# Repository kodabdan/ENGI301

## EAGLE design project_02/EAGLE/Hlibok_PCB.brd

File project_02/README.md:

Etch-A-Sketch PCB by Brendan Hlibok, 2023

This project consists of a 4-layer PCB designed by Brendan Hlibok using EAGLE software.
The PCB functions as an etch-a-sketch when manufactured. More specific information on this can be found in the
powerpoint presentation under project_02/docs.

The board is 4" tall and 5" wide. The library, schematic, and board layout files can be found in the "EAGLE" folder, and the gerber files for manufacturing
the PCB. The "docs" folder contains descriptive information such as images of important layers, the schematics,
the board layout, and a bill of materials for the product. The bill of materials is in .txt and .csv format, where the .txt
file came straight from the EAGLE software, and the excel file has more specific info regarding component parts.

The board file can be uploaded to manufacturing sites to check quotes for building the board. The site used for this project was
MacroFab.

This project was completed as a part of the ENGI 301 course at Rice University taught by Erik Welsh, who designed the circuit
for the PCB in this file.

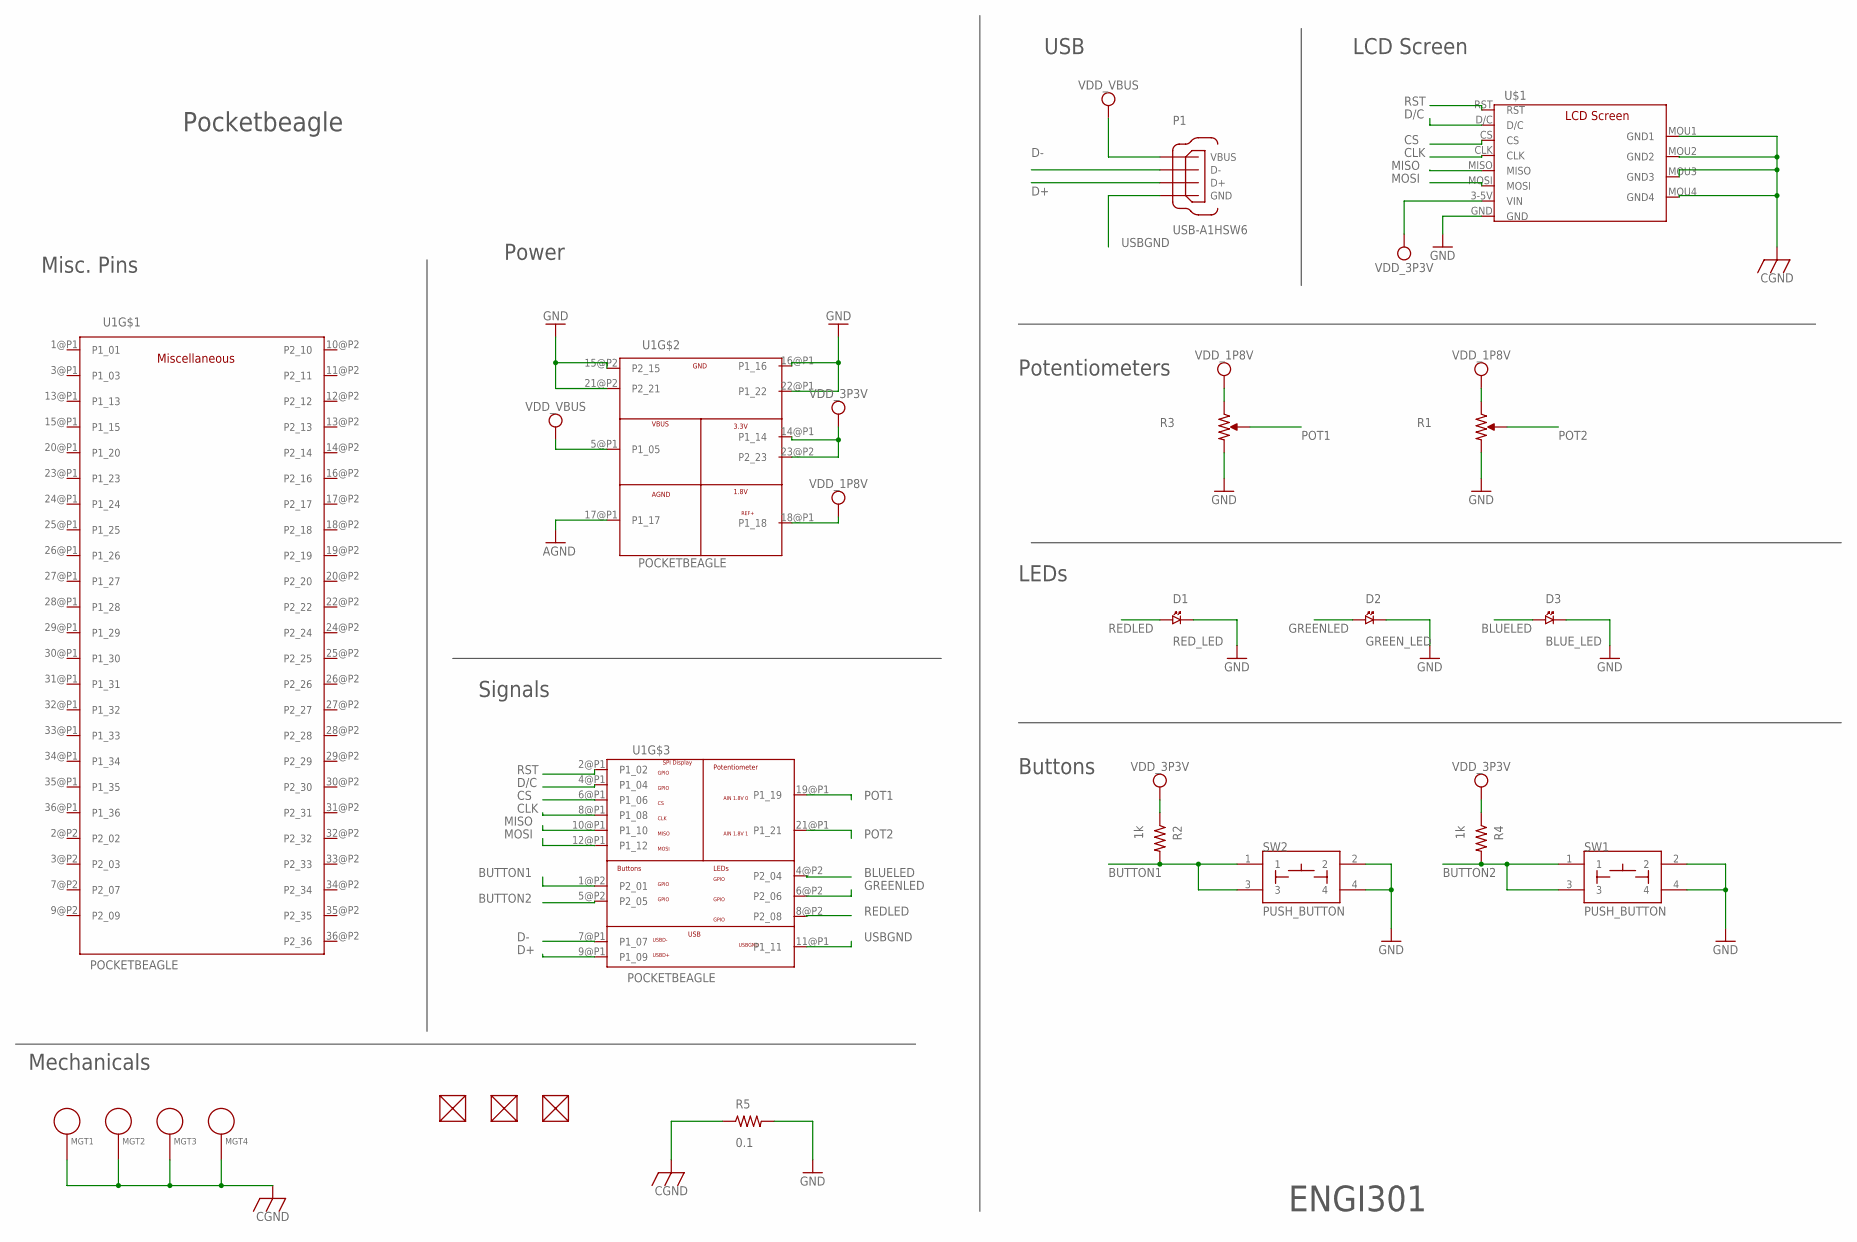
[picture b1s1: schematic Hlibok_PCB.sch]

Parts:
D1: RED_LED; EIA-STD
D2: GREEN_LED; EIA-STD
D3: BLUE_LED; EIA-STD
FUD1, FUD2, FUD3: FIDUCIAL; FIDUCIAL_40MIL
MGT1, MGT2, MGT3, MGT4: MOUNTING_HOLE
P1: USB-A1HSW6; USB
R1, R3: POTENTIOMETER; POT-PO90S
R2, R4: 1k; R0603
R5: 0.1; R0805
SW1, SW2: PUSH_BUTTON; BUTTON_12.5MM
U1: POCKETBEAGLE
U$1: SCREEN

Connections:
BLUELED: D3.ANODE, U1.4@P2 (P2_04)
BUTTON1: R2.2, SW2.1, SW2.3, U1.1@P2 (P2_01)
BUTTON2: R4.2, SW1.1, SW1.3, U1.5@P2 (P2_05)
CGND: MGT1.P$1, MGT2.P$1, MGT3.P$1, MGT4.P$1, R5.1, U$1.MOU1 (GND1), U$1.MOU2 (GND2), U$1.MOU3 (GND3), U$1.MOU4 (GND4)
CLK: U1.8@P1 (P1_08), U$1.CLK
CS: U1.6@P1 (P1_06), U$1.CS
D+: P1.3 (D+), U1.9@P1 (P1_09)
D-: P1.2 (D-), U1.7@P1 (P1_07)
D/C: U1.4@P1 (P1_04), U$1.D/C
GND: D1.CATHODE, D2.CATHODE, D3.CATHODE, R1.CW, R3.CW, R5.2, SW1.2, SW1.4, SW2.2, SW2.4, U1.15@P2 (P2_15), U1.16@P1 (P1_16), U1.17@P1 (P1_17), U1.21@P2 (P2_21), U1.22@P1 (P1_22), U$1.GND
GREENLED: D2.ANODE, U1.6@P2 (P2_06)
MISO: U1.10@P1 (P1_10), U$1.MISO
MOSI: U1.12@P1 (P1_12), U$1.MOSI
POT1: R3.S, U1.19@P1 (P1_19)
POT2: R1.S, U1.21@P1 (P1_21)
REDLED: D1.ANODE, U1.8@P2 (P2_08)
RST: U1.2@P1 (P1_02), U$1.RST
USBGND: P1.4 (GND), U1.11@P1 (P1_11)
VDD_1P8V: R1.CCW, R3.CCW, U1.18@P1 (P1_18)
VDD_3P3V: R2.1, R4.1, U1.14@P1 (P1_14), U1.23@P2 (P2_23), U$1.3-5V (VIN)
VDD_5V: P1.1 (VBUS), U1.5@P1 (P1_05)

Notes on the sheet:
Power
Signals
Misc. Pins
Pocketbeagle
USB
Potentiometers
LEDs
Buttons
LCD Screen
ENGI301
Mechanicals

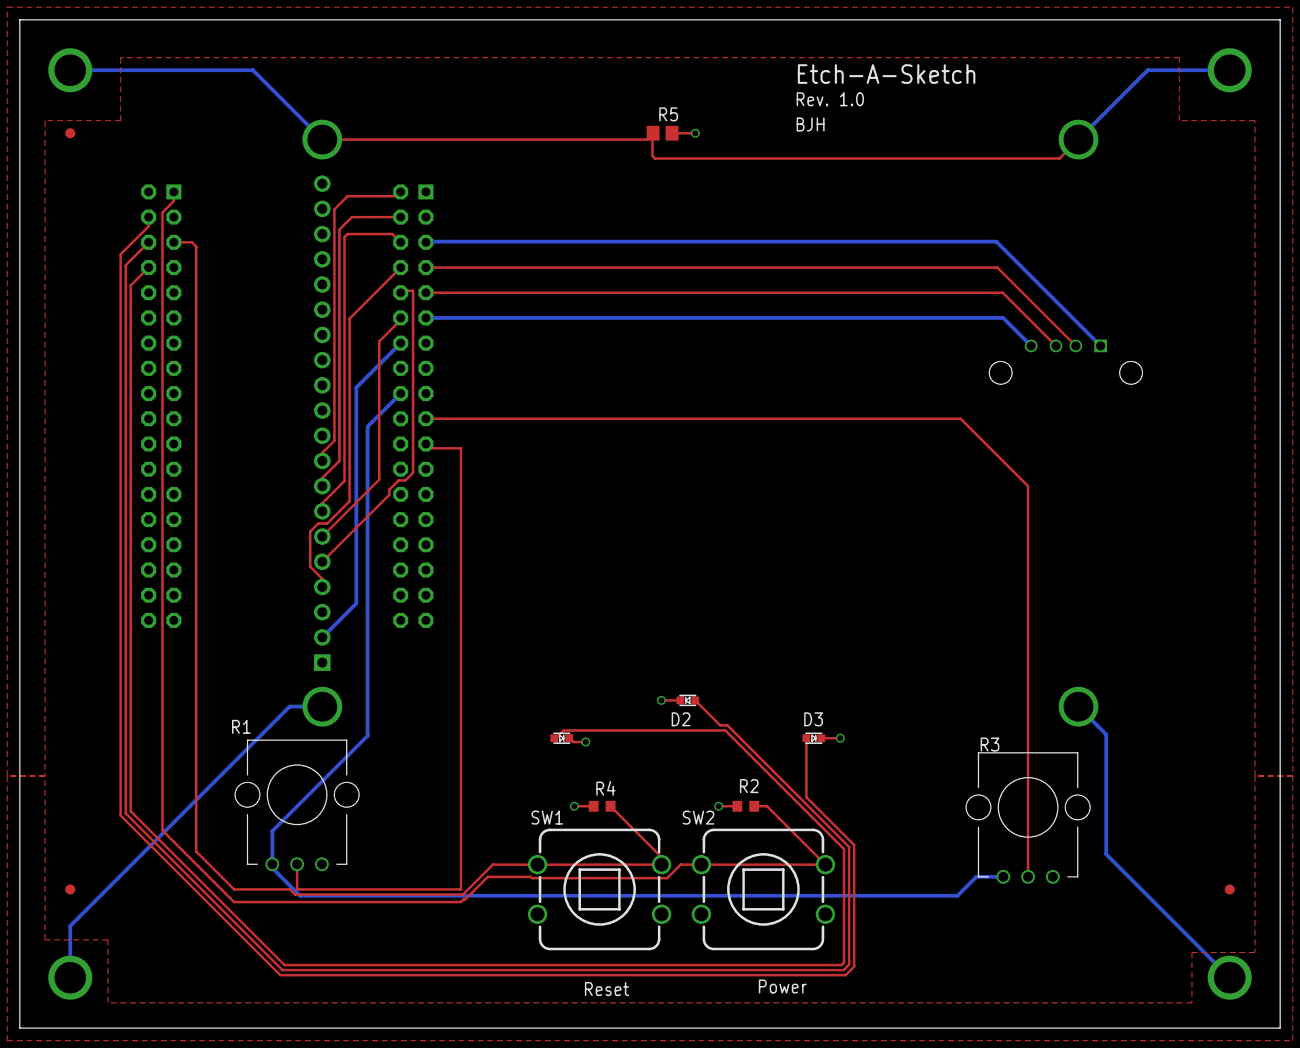
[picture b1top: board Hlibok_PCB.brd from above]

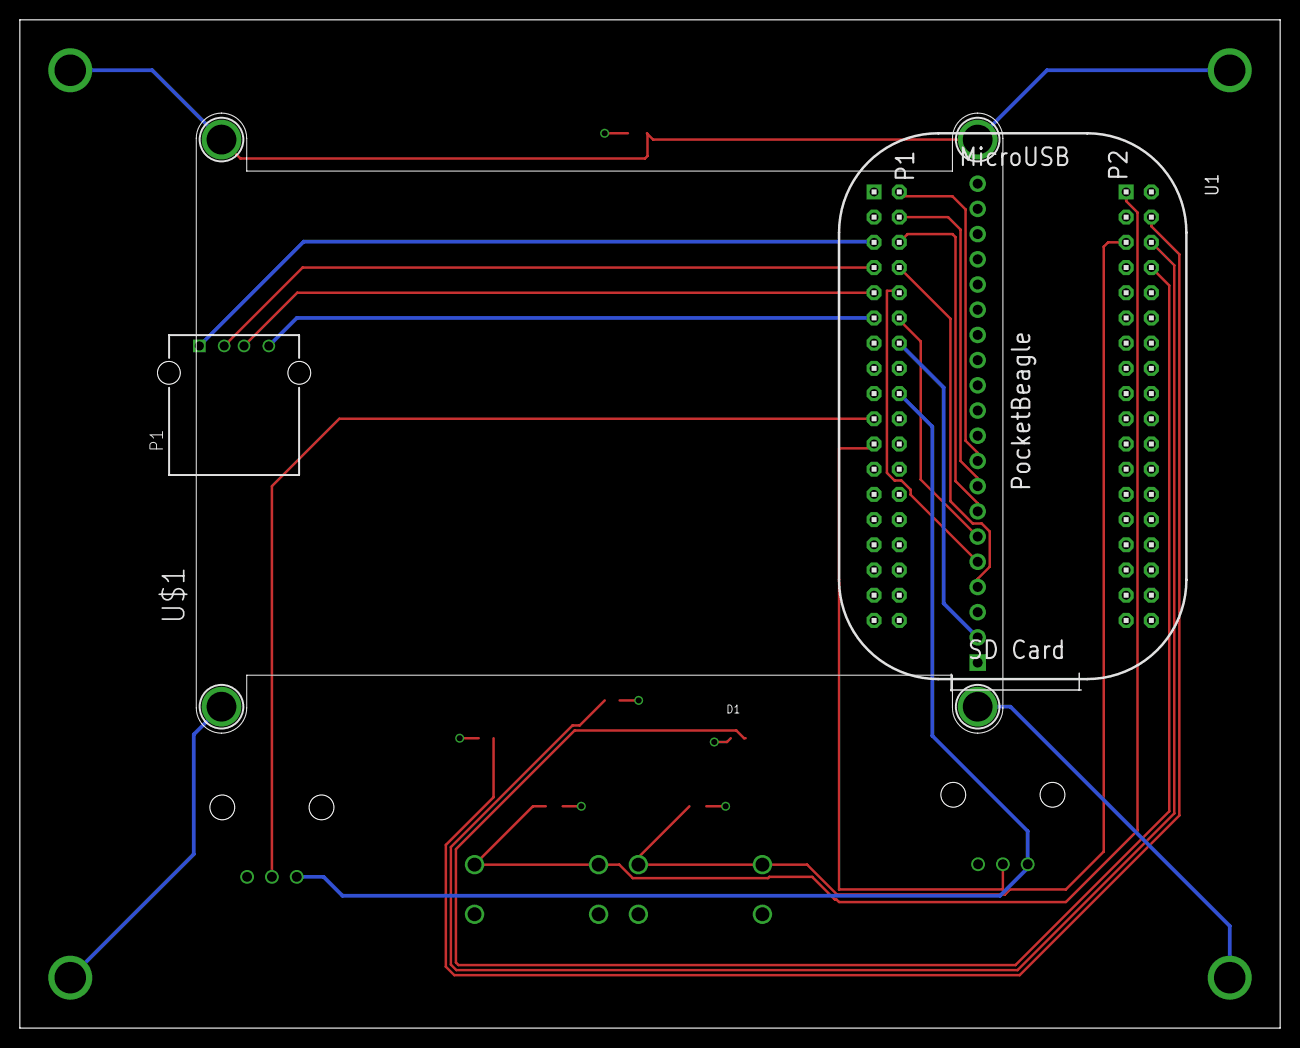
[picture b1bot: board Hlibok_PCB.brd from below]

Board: 4 copper layers, 127.0 x 101.6 mm, 20 parts (3 on the bottom side), 21 nets.

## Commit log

2023-09-26 Create createpython
2023-09-28 Delete python/simple_calc (1).py
    Incorrect file
2023-09-28 Delete python/createpython
    unnecessary file
2023-10-13 Create docs
2023-10-13 Create folder create
2023-11-08 adding project 1 files
2023-11-15 Create run
2023-12-15 Create Creation File
2023-12-15 Create creation
2023-12-15 Create Create eagle
2023-12-15 Create creationdocs
2023-12-15 Create creategerbers
